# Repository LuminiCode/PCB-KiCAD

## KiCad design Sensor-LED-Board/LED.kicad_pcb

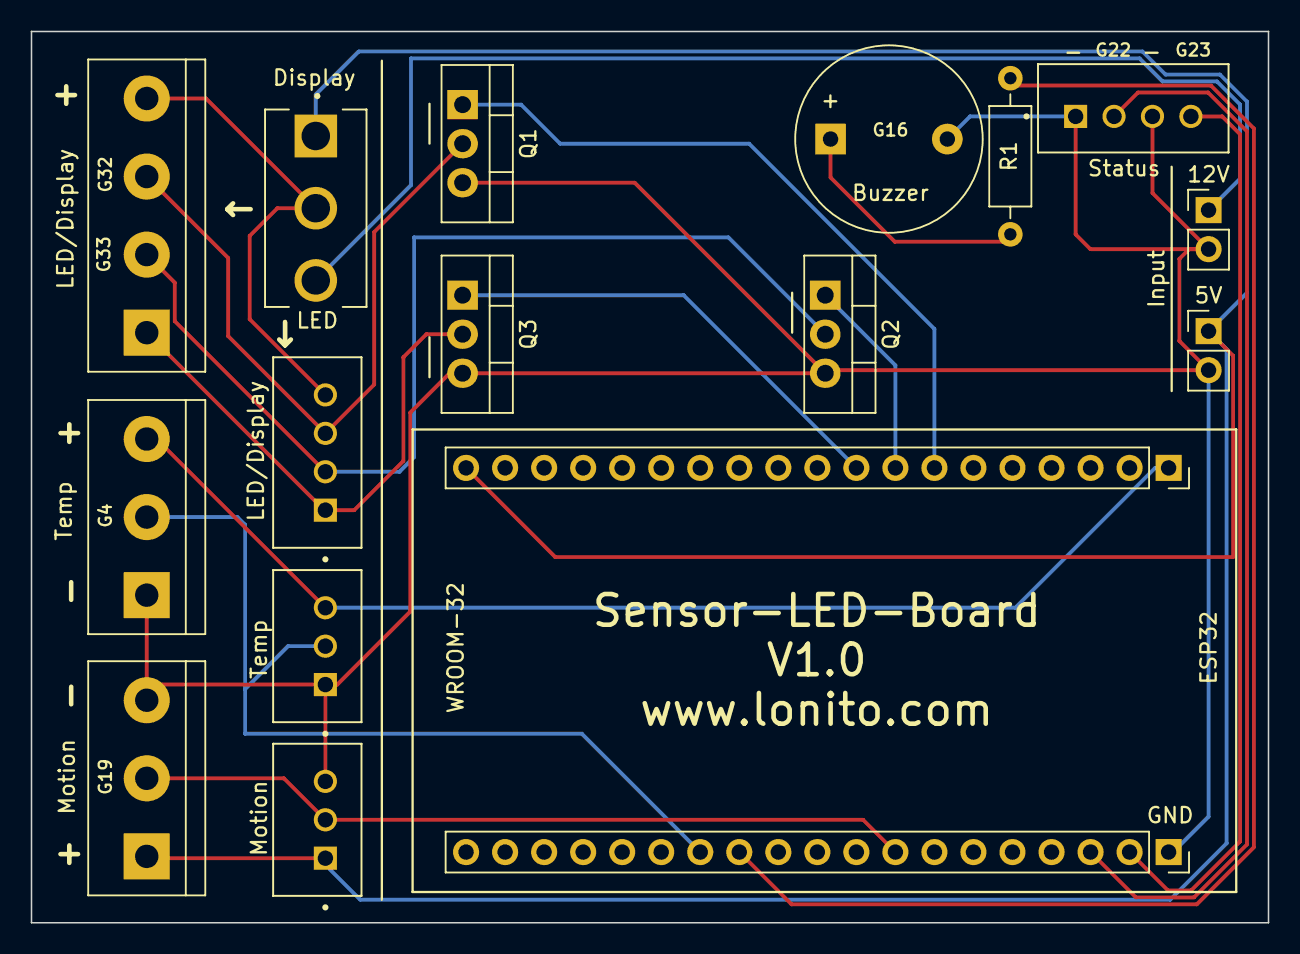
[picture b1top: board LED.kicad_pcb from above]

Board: 2 copper layers, 80.5 x 58.0 mm, 17 parts (0 on the bottom side), 17 nets.

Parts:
5V: Conn_01x02_Male; PinHeader_1x02_P2.54mm_Vertical
12V: 12V; PinHeader_1x02_P2.54mm_Vertical
Buzzer: Buzzer; Buzzer_12x9.5RM7.6
ESP32: Conn_01x19_Female_Esp32-2; PinSocket_1x19_P2.54mm_Vertical
LED/Display: B4B-XH-A(LF)(SN); JST_B4B-XH-A(LF)(SN)
LED/Display#2: Screw_Terminal_01x04; TerminalBlock_bornier-4_P5.08mm
Motion: Motion Sensor Out; JST_B3B-XH-A(LF)(SN)
Motion#2: Screw_Terminal_01x03-1; TerminalBlock_bornier-3_P5.08mm
Q1, Q2, Q3: IRLZ34N; TO-220-3_Vertical
R1: R; R_Axial_DIN0207_L6.3mm_D2.5mm_P10.16mm_Horizontal
SW1: SW_Push_SPDT; SW_500SSP1S2M2QEA
Status: B4B-XH-A(LF)(SN); JST_B4B-XH-A(LF)(SN)
Temp: Temp Sensor Out; JST_B3B-XH-A(LF)(SN)
Temp#2: Screw_Terminal_01x03-2; TerminalBlock_bornier-3_P5.08mm
WROOM-32: Conn_01x19_Female_Esp32-1; PinSocket_1x19_P2.54mm_Vertical

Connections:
unnamed: 5V.1, ESP32.19 (5V), Motion.1, Motion#2.1, SW1.1 (A)
unnamed: 12V.1, SW1.3 (C)
unnamed: 5V.2, 12V.2, Buzzer.2 (+), Motion.3, Motion#2.3, Q1.3 (S), Q2.3 (S), Q3.3 (S), Status.1, Status.3, Temp.1, Temp#2.1, WROOM-32.1 (GND)
unnamed: Buzzer.1 (-), R1.1
unnamed: Status.4, WROOM-32.2 (G23)
unnamed: Status.2, WROOM-32.3 (F22)
unnamed: Motion.2, Motion#2.2, WROOM-32.8 (G19)
unnamed: R1.2, WROOM-32.12 (G16)
unnamed: Temp.2, Temp#2.2, WROOM-32.13 (G4)
unnamed: ESP32.1 (3V3), Temp.3, Temp#2.3
unnamed: ESP32.7 (G32), Q1.1 (G)
unnamed: ESP32.8 (G33), Q2.1 (G)
unnamed: ESP32.9 (G25), Q3.1 (G)
unnamed: LED/Display.1, LED/Display#2.1, Q3.2 (D)
unnamed: LED/Display.2, LED/Display#2.2, Q2.2 (D)
unnamed: LED/Display.3, LED/Display#2.3, Q1.2 (D)
unnamed: LED/Display.4, LED/Display#2.4, SW1.2 (B)

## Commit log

2022-12-26 Create Sensor-LED-Board
